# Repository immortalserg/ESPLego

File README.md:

# ESPLego
## Платы для модернизации блоков с двигателями конструкторов Lego

Есть старые Lego машинки с моторчиком? Модернизировать с помощью EspLego - плата с wi-fi модулем ESP8266 и драйвером управления мотором L298P позволяет управлять вашей машинкой по wi-fi, а контроллер заряда позволяет заменить батарейки AA на 3,7В Li-ion батарею.

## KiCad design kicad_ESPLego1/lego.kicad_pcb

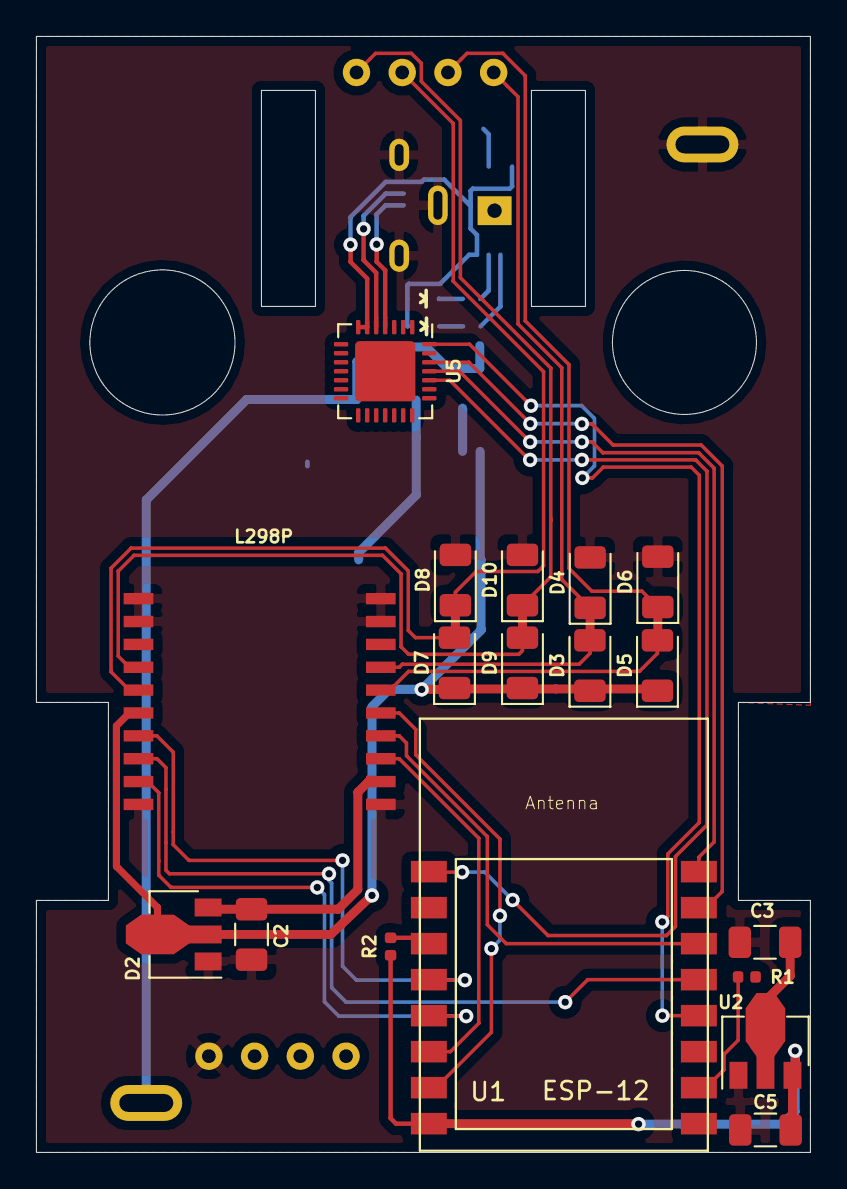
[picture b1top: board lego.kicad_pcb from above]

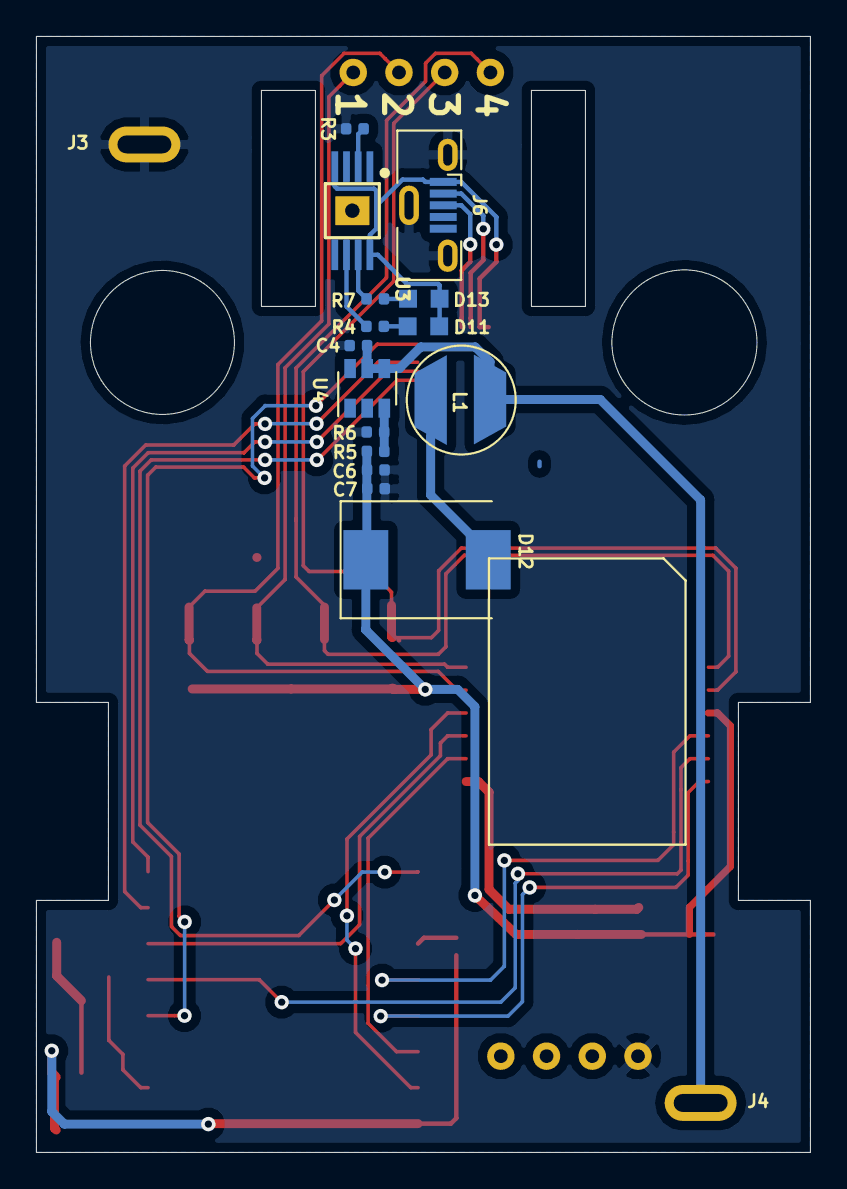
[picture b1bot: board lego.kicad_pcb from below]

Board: 2 copper layers, 43.0 x 62.0 mm, 37 parts (15 on the bottom side), 32 nets.

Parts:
C2: 47 µF; C_1206_3216Metric
C3, C5: TAJA106K016RNJ; C_1206_3216Metric
C4, C6: 22uF; C_0402_1005Metric
C7: 10uF; C_0402_1005Metric
D2: HT7550; SOT-89-3
D3, D4, D5, D6, D7, D8, D9, D10: 11eqs06; D_1206_3216Metric
D11, D13: LED0603; LED-0603
D12: 1N5822; D_SMC
IC1: L298P; POWERSO20
J1, J5: Conn_01x04_Male; pin4_2,54
J3, J4: Conn_01x01_Male; con1_2,54
J6: USB_B_Micro; USB_Micro-B_Molex-105133-0001
L1: 22uH; CD54
R1, R2: 10 k; R_0402_1005Metric
R3: Rprog; R_0402_1005Metric
R4, R7: 1k; R_0402_1005Metric
R5: 16k; R_0402_1005Metric
R6: 2.2k; R_0402_1005Metric
U1: ESP-12
U2: HT7533-1; SOT-89-3
U3: TP4056; PPSOP8
U4: MT3608; SOT-23-6
U5: CP2102N-A01-GQFN24; QFN-28-1EP_5x5mm_P0.5mm_EP3.35x3.35mm

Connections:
3,3V: C5.1, J1.3, R2.1, U1.8, U2.3
+6V: C3.1, C6.1, C7.1, D2.2, D3.1, D5.1, D7.1, D9.1, D12.1, IC1.6, R5.1, U2.2
DTR: J1.1, U1.12, U5.28
GND: C2.2, C3.2, C4.2, C5.2, C6.2, C7.2, D2.1, D4.2, D6.2, D8.2, D10.2, IC1.1, IC1.2, IC1.10, IC1.11, IC1.19, IC1.20, J1.4, J3.1, J6.5, J6.6, R1.1, R3.2, R6.2, U1.9, U2.1, U3.3, U4.2, U5.3, U5.29
unnamed: C2.1, D2.3, IC1.12
unnamed: C4.1, J4.1, L1.1, U3.5, U4.4, U4.5
unnamed: D3.2, D4.1, IC1.17, J5.4
unnamed: D5.2, D6.1, IC1.16, J5.3
unnamed: D7.2, D8.1, IC1.5, J5.2
unnamed: D9.2, D10.1, IC1.4, J5.1
unnamed: D11.A, D13.A, J6.1, U3.4, U3.8, U5.6, U5.7
unnamed: D11.C, R4.2
unnamed: D12.2, L1.2, U4.1
unnamed: D13.C, R7.2
unnamed: IC1.7, U1.4
unnamed: IC1.8, U1.13
unnamed: IC1.9, U1.5
unnamed: IC1.13, U1.6
unnamed: IC1.14, U1.14
unnamed: IC1.15, U1.7
unnamed: J1.2, U1.11
unnamed: J6.2, U5.5
unnamed: J6.3, U5.4
unnamed: R1.2, U1.10
unnamed: R2.2, U1.3
unnamed: R3.1, U3.2
unnamed: R4.1, U3.6
unnamed: R5.2, R6.1, U4.3
unnamed: R7.1, U3.7
RTS: U1.1, U5.24
RXD: U1.16, U5.25
TXD: U1.15, U5.26

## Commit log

2018-11-01 a msg
